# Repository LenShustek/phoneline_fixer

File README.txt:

This is a very strange box that solves a very strange
   problem with my Panasonic KX-T30810 PBX phone switch.

   When AT&T changed one of our three Central Office lines, it didn't work
   with my venerable 30-year-old Panasonic 3x8 phone switch. There was no
   dial tone, no matter which of the CO ports on the switch it was plugged
   into. But the new line works fine with a regular phone, so of course the
   AT&T technician said there's nothing wrong, and closed the service call
   with "no trouble found".

   After much experimentation, and an online discussion at
   https://sundance-communications.com/forum/ubbthreads.php/topics/638453/1
   with a group of experienced phone installers, the diagnosis was that
   something the phone switch is doing just after the phone goes off-hook
   is being interpreted on that new CO line -- and *only* on that CO line
   -- as a "1" being dialed. That stops the dial tone, and any phone number
   dialed after that elicits the error message "You don't need to dial a 1
   to reach that number."

   Rather than try to beg/demand a new line from AT&T that is different in
   some way I can't describe to them, I built a small box that sits between
   that CO line and the phone switch and has variously implemented different
   strategies to fix the problem:

   (1) When the switch takes the line off-hook, the box quickly
   breaks the connection to the CO line and simultaneously puts
   a 500 ohm shunt resistor across the line to maintain the
   off-hook condition. It waits 600 milliseconds for the switch to do
   whatever it does that the CO is interpreting as a dialed digit "1", then
   it reconnects the switch to the CO line and removes the shunt.
  
   This worked for a couple of years, until AT&T changed to line to some other
   "fake copper pair" digital simulation (PG? DPD?), which seems to interpret 
   reconnecting the PBX as enough noise to signal a "1". So we switched to a 
   second strategy.

   (2) When the switch takes the line off-hook, the box quickly puts a
   33uf 450V capacitor (in parallel with a 33K bleed resistor)
   across the tip and ring lines, suppressing whatever funny thing
   the phone switch is doing that is interpreted as a pulse-dialed "1".
   It waits 750 msec and then removes the capacitor.
   
   We also changed to computing the voltage across tip and ring by 
   subtracting the voltages as measured relative to ground. That makes us
   independent from the ground reference of the CO loop, which has changed.
   
   This scheme now works -- but we'll see for how long!

   If anyone else has had this problem, or has any insight into what the 
   switch is doing "wrong" and why it only causes a problem on one of the 
   CO lines, I'd love to hear about it. 

Len Shustek September 29, 2020 
V2.0, January 12, 2022

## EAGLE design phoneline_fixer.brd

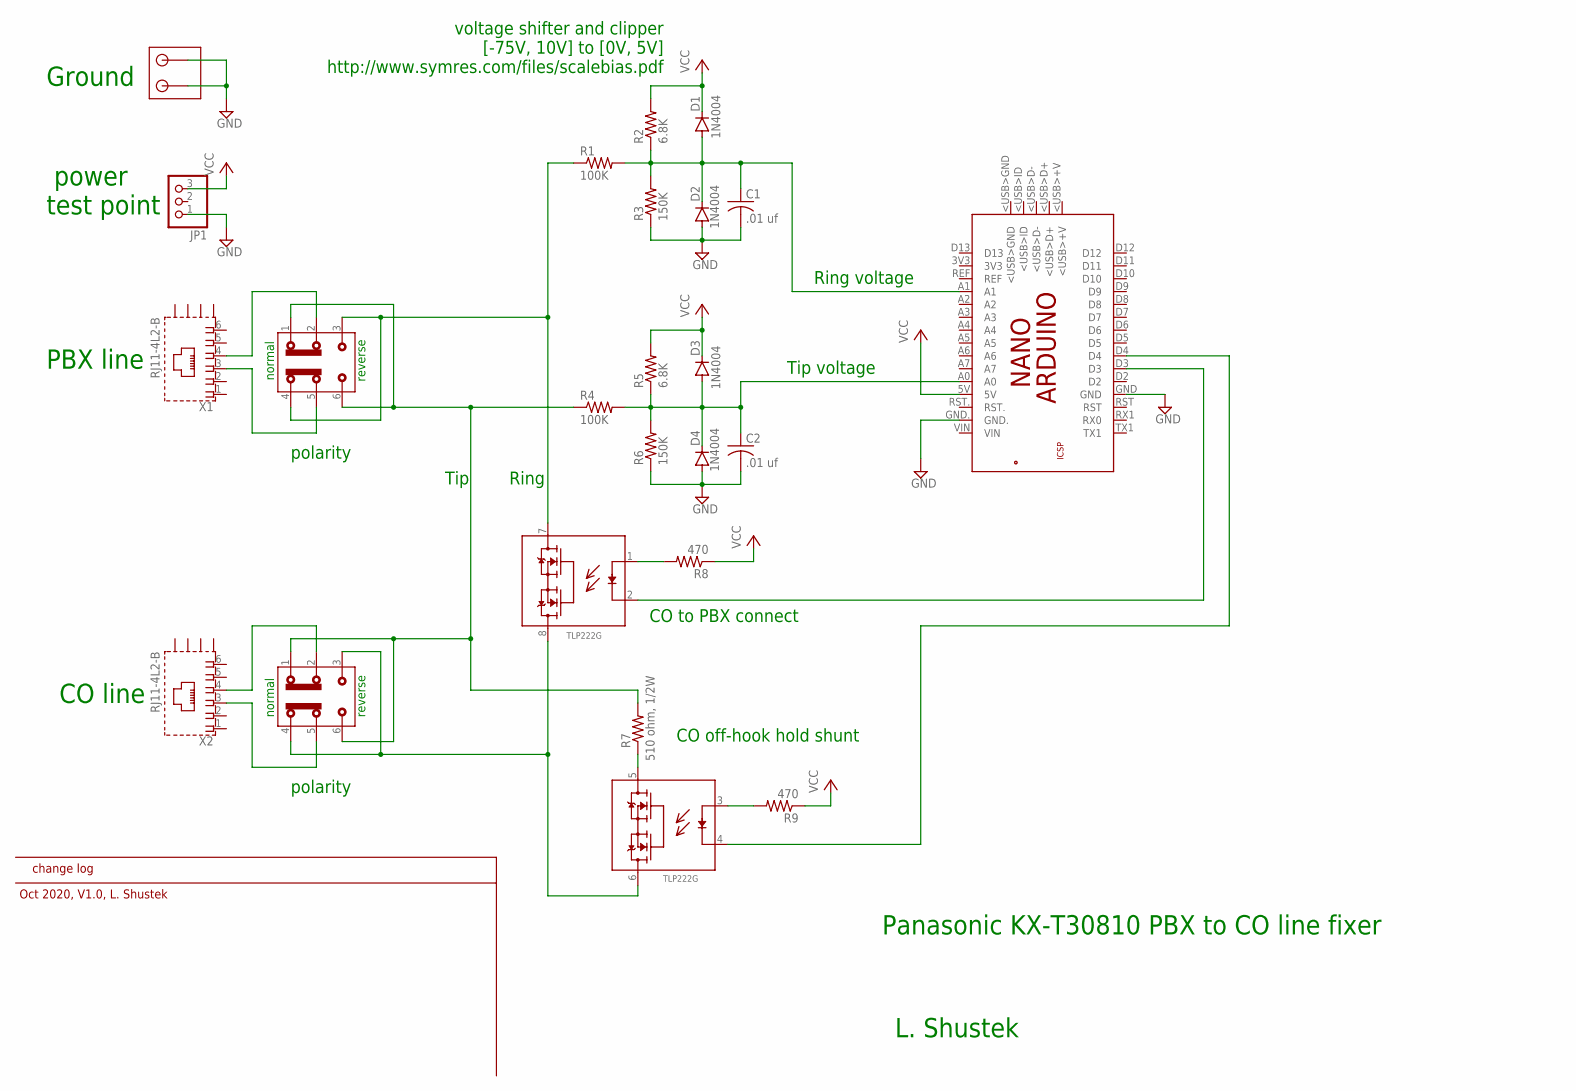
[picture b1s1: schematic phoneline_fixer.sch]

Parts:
C1, C2: .01 uf; C050-025X075
D1, D2, D3, D4: 1N4004; DO41-10
JP1: PINHD-1X3; 1X03
PCB1: ARDUINO_NANO
R1, R4: 100K; 0207/12
R2, R5: 6.8K; 0207/12
R3, R6: 150K; 0207/12
R7: 510 ohm, 1/2W; 0414/15
R8, R9: 470; 0207/12
U$1: TLP222G; DIL08
U$2: CONNECTOR-2PINTHIN; CONNECTOR-2PIN-5MM_THIN
U$3, U$4: SWITCH_SLIDE_DPDT
X1, X2: RJ11-4L2-B; RJ11-SHIELD2

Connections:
GND: C1.2, C2.2, D2.A, D4.A, JP1.1, PCB1.GND, PCB1.GND., R3.1, R6.1, U$2.P$1, U$2.P$2
unnamed: C1.1, D1.A, D2.C, PCB1.A1, R1.2, R2.1, R3.2
unnamed: C2.1, D3.A, D4.C, PCB1.A0, R4.2, R5.1, R6.2
unnamed: R7.1, U$1.5 (D2)
unnamed: R8.2, U$1.1 (A)
unnamed: R9.2, U$1.3 (A)
unnamed: U$4.5, X2.3
unnamed: U$4.2, X2.4
unnamed: PCB1.D3, U$1.2 (C)
unnamed: PCB1.D4, U$1.4 (C)
unnamed: R4.1, R7.2, U$3.1, U$3.6, U$4.1, U$4.6
unnamed: U$1.6 (D1), U$1.8 (D1), U$4.3, U$4.4
unnamed: U$3.5, X1.3
unnamed: U$3.2, X1.4
unnamed: R1.1, U$1.7 (D2), U$3.3, U$3.4
VCC: D1.C, D3.C, JP1.3, PCB1.5V, R2.2, R5.2, R8.1, R9.1

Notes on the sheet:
CO line
PBX line
Tip
Ring
Panasonic KX-T30810 PBX to CO line fixer
L. Shustek
CO off-hook hold shunt
voltage shifter and clipper [-75V, 10V] to [0V, 5V] http://www.symres.com/files/scalebias.pdf
CO to PBX connect
Ring voltage
Tip voltage
Ground
polarity
power test point
change log
Oct 2020, V1.0, L. Shustek
reverse
normal

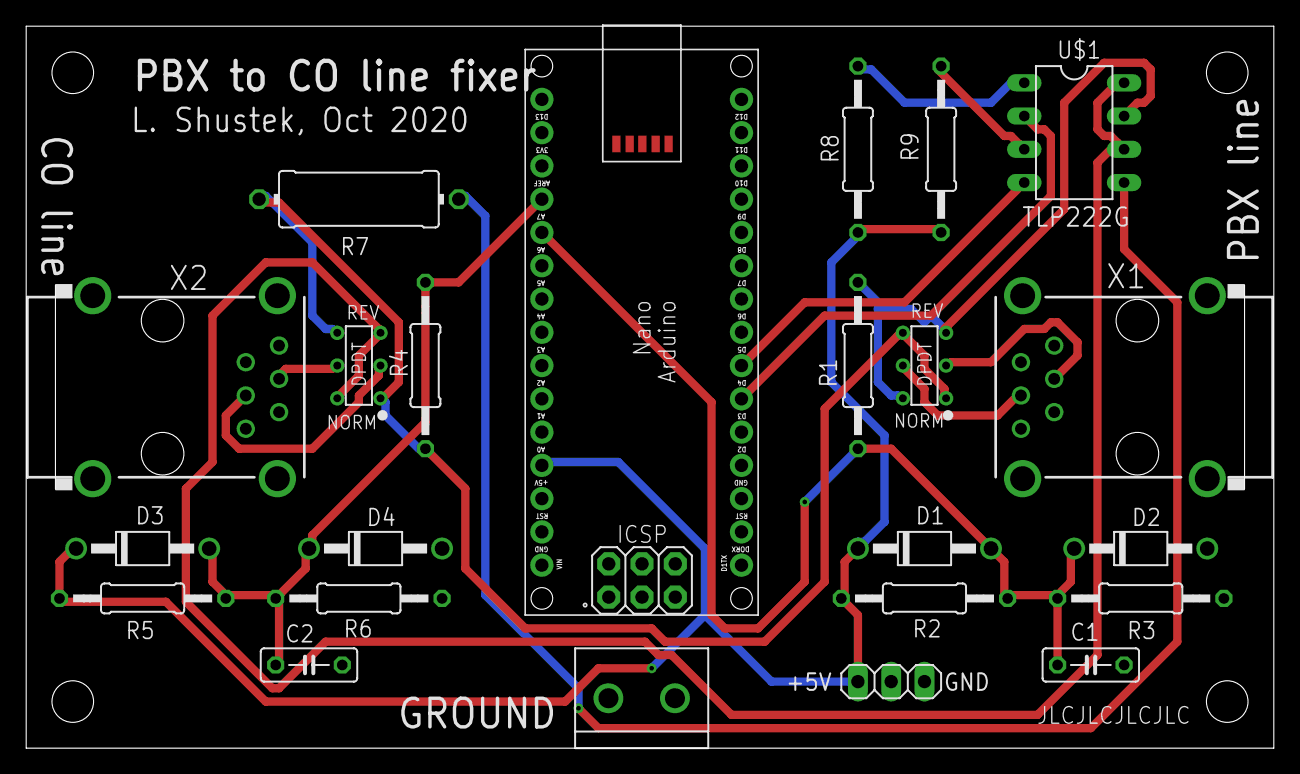
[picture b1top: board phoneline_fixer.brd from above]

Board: 2 copper layers, 95.2 x 55.1 mm, 23 parts (0 on the bottom side), 16 nets.

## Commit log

2020-09-30 initial release
    Fix a strange problem with the Panasonic KX-T30810 PBX phone switch.
2020-10-08 Production version with PC board
2022-01-13 Document version 2.0
